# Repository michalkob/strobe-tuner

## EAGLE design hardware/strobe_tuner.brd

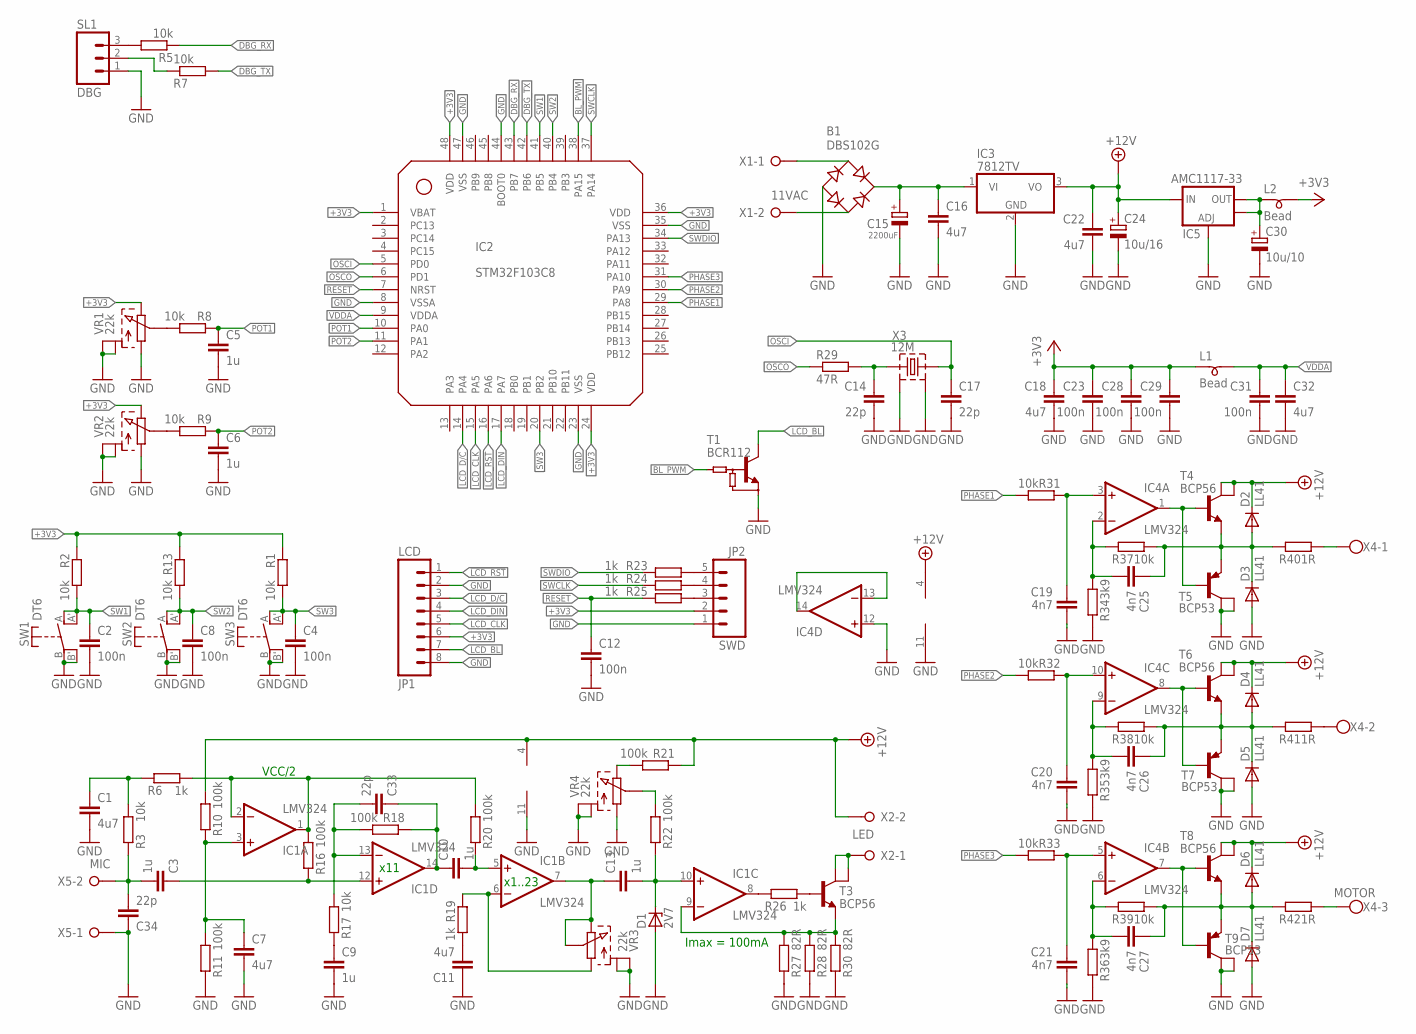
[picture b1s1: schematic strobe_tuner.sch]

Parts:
B1: DBS102G; DBS
C1, C7, C11, C16, C18, C22, C32: 4u7; 1206
C2, C4, C8, C12, C23, C28, C29, C31: 100n; 0805
C3, C5, C6, C9, C10, C13: 1u; 1206
C14, C17, C33, C34: 22p; 0805
C15: 2200uF; E5-13
C19, C20, C21, C25, C26, C27: 4n7; 0805
C24: 10u/16; B/3528-21W
C30: 10u/10; A/3216-18R
D1: 2V7; SOT23
D2, D3, D4, D5, D6, D7: LL41; SOD80C
IC1, IC4: LMV324; SO14
IC2: STM32F103C8; LQFP48
IC3: 7812TV; TO220V
IC5: AMC1117-33; SOT223
JP1: LCD; 1X08
JP2: SWD; 1X05_LOCK_LONGPADS
L1, L2: Bead; 0805
R1, R2, R3, R5, R7, R8, R9, R13, R17, R31, R32, R33, R37, R38, R39: 10k; 0805
R6, R19, R23, R24, R25, R26: 1k; 0805
R10, R11, R16, R18, R20, R21, R22: 100k; 0805
R27, R28, R30: 82R; 0805
R29: 47R; 0805
R34, R35, R36: 3k9; 0805
R40, R41, R42: 1R; 0805
SL1: DBG; 03P
SW1, SW2, SW3: DT6; D6R
T1: BCR112; SOT23
T3, T4, T6, T8: BCP56; SOT223
T5, T7, T9: BCP53; SOT223
VR1, VR2, VR3, VR4: 22k; R122KNP
X1: 11VAC; W237-132
X2: LED; W237-132
X3: 12M; CPFX-104
X4: MOTOR; W237-103
X5: MIC; W237-132

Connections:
!LCD_RST: IC2.16 (PA6), JP1.1
+3V3: C18.1, C23.1, C28.1, C29.1, IC2.1 (VBAT), IC2.24 (VDD), IC2.36 (VDD), IC2.48 (VDD), JP1.6, JP2.2, L1.2 (1), L2.1 (2), R1.1, R2.1, R13.1, VR1.CW (E), VR2.CW (E)
+12V: C22.1, C24.+, D2.C, D4.C, D6.C, IC1.4 (V+), IC3.3 (VO), IC4.4 (V+), IC5.3 (IN), R10.2, R21.1, T4.2 (C), T4.4 (C1), T6.2 (C), T6.4 (C1), T8.2 (C), T8.4 (C1), X2.2
BL_PWM: IC2.38 (PA15), T1.1 (B)
DBG_RX: IC2.43 (PB7), R5.1
DBG_TX: IC2.42 (PB6), R7.2
GND: B1.-, C1.2, C2.2, C4.2, C5.2, C6.2, C7.2, C8.2, C9.2, C11.1, C12.2, C14.2, C15.-, C16.2, C17.2, C18.2, C19.2, C20.2, C21.2, C22.2, C23.2, C24.-, C28.2, C29.2, C30.-, C31.2, C32.2, C34.1, D1.1 (A), D3.A, D5.A, D7.A, IC1.11 (V-), IC2.8 (VSSA), IC2.23 (VSS), IC2.35 (VSS), IC2.44 (BOOT0), IC2.47 (VSS), IC3.2 (GND), IC4.11 (V-), IC4.12 (+IN), IC5.1 (ADJ), JP1.2, JP1.8, JP2.1, R11.1, R27.1, R28.1, R30.1, R34.1, R35.1, R36.1, SL1.1, SW1.B (B1), SW1.B' (B2), SW2.B (B1), SW2.B' (B2), SW3.B (B1), SW3.B' (B2), T1.2 (E), T5.2 (C), T5.4 (C1), T7.2 (C), T7.4 (C1), T9.2 (C), T9.4 (C1), VR1.CCW (A), VR1.P$1 (CASE1), VR1.P$2 (CASE2), VR2.CCW (A), VR2.P$1 (CASE1), VR2.P$2 (CASE2), VR3.P$1 (CASE1), VR3.P$2 (CASE2), VR4.CCW (A), VR4.P$1 (CASE1), VR4.P$2 (CASE2), X3.2 (G1), X3.4 (G2), X5.1
LCD_BL: JP1.7, T1.3 (C)
LCD_CLK: IC2.15 (PA5), JP1.5
LCD_D/C: IC2.14 (PA4), JP1.3
LCD_DIN: IC2.17 (PA7), JP1.4
unnamed: C19.1, IC4.3 (+IN), R31.1
unnamed: C20.1, IC4.10 (+IN), R32.1
unnamed: C21.1, IC4.5 (+IN), R33.1
unnamed: C27.1, D6.A, D7.C, R39.2, R42.1, T8.3 (E), T9.3 (E)
unnamed: C1.1, R3.2, R6.1
unnamed: C7.1, IC1.3 (+IN), R10.1, R11.2
unnamed: C3.2, C34.2, R3.1, X5.2
unnamed: C11.2, R19.2
unnamed: R26.2, T3.1 (B)
unnamed: C9.1, R17.1
unnamed: IC4.1 (OUT), T4.1 (B), T5.1 (B)
unnamed: C25.2, IC4.2 (-IN), R34.2, R37.1
unnamed: C26.1, D4.A, D5.C, R38.2, R41.1, T6.3 (E), T7.3 (E)
unnamed: IC4.8 (OUT), T6.1 (B), T7.1 (B)
unnamed: C26.2, IC4.9 (-IN), R35.2, R38.1
unnamed: C33.2, IC1.13 (-IN), R17.2, R18.2
unnamed: IC4.7 (OUT), T8.1 (B), T9.1 (B)
unnamed: C27.2, IC4.6 (-IN), R36.2, R39.1
unnamed: IC1.9 (-IN), R27.2, R28.2, R30.2, T3.3 (E)
unnamed: T3.2 (C), T3.4 (C1), X2.1
unnamed: IC1.8 (OUT), R26.1
unnamed: R40.2, X4.1
unnamed: R41.2, X4.2
unnamed: R42.2, X4.3
unnamed: IC1.1 (OUT), IC1.2 (-IN), R6.2, R16.2, R20.2
unnamed: C10.1, C33.1, IC1.14 (OUT), R18.1
unnamed: C3.1, IC1.12 (+IN), R16.1
unnamed: C13.2, D1.3 (C), IC1.10 (+IN), R22.1
unnamed: IC1.6 (-IN), R19.1, VR3.CCW (A)
unnamed: C13.1, IC1.7 (OUT), VR3.CW (E), VR3.SLIDER (S)
unnamed: R21.2, VR4.CW (E)
unnamed: R9.2, VR2.SLIDER (S)
unnamed: C10.2, IC1.5 (+IN), R20.1
unnamed: R22.2, VR4.SLIDER (S)
unnamed: R7.1, SL1.2
unnamed: R8.2, VR1.SLIDER (S)
unnamed: JP2.5, R23.1
unnamed: C30.+, IC5.2 (OUT), IC5.4 (OUT), L2.2 (1)
unnamed: C25.1, D2.A, D3.C, R37.2, R40.1, T4.3 (E), T5.3 (E)
unnamed: B1.AC1, X1.1
unnamed: B1.AC2, X1.2
unnamed: IC4.13 (-IN), IC4.14 (OUT)
unnamed: R5.2, SL1.3
unnamed: JP2.4, R24.1
unnamed: JP2.3, R25.1
unnamed: C14.1, R29.2, X3.1
OSCI: C17.1, IC2.5 (PD0), X3.3 (2)
OSCO: IC2.6 (PD1), R29.1
PHASE1: IC2.29 (PA8), R31.2
PHASE2: IC2.30 (PA9), R32.2
PHASE3: IC2.31 (PA10), R33.2
POT1: C5.1, IC2.10 (PA0), R8.1
POT2: C6.1, IC2.11 (PA1), R9.1
RESET: C12.1, IC2.7 (NRST), R25.2
SW1: C2.1, IC2.41 (PB5), R2.2, SW1.A (A1), SW1.A' (A2)
SW2: C8.1, IC2.40 (PB4), R13.2, SW2.A (A1), SW2.A' (A2)
SW3: C4.1, IC2.20 (PB2), R1.2, SW3.A (A1), SW3.A' (A2)
SWCLK: IC2.37 (PA14), R24.2
SWDIO: IC2.34 (PA13), R23.2
VDDA: C31.1, C32.1, IC2.9 (VDDA), L1.1 (2)
VIN: B1.+, C15.+, C16.1, IC3.1 (VI)

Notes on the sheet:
VCC/2
x11
x1..23
Imax = 100mA

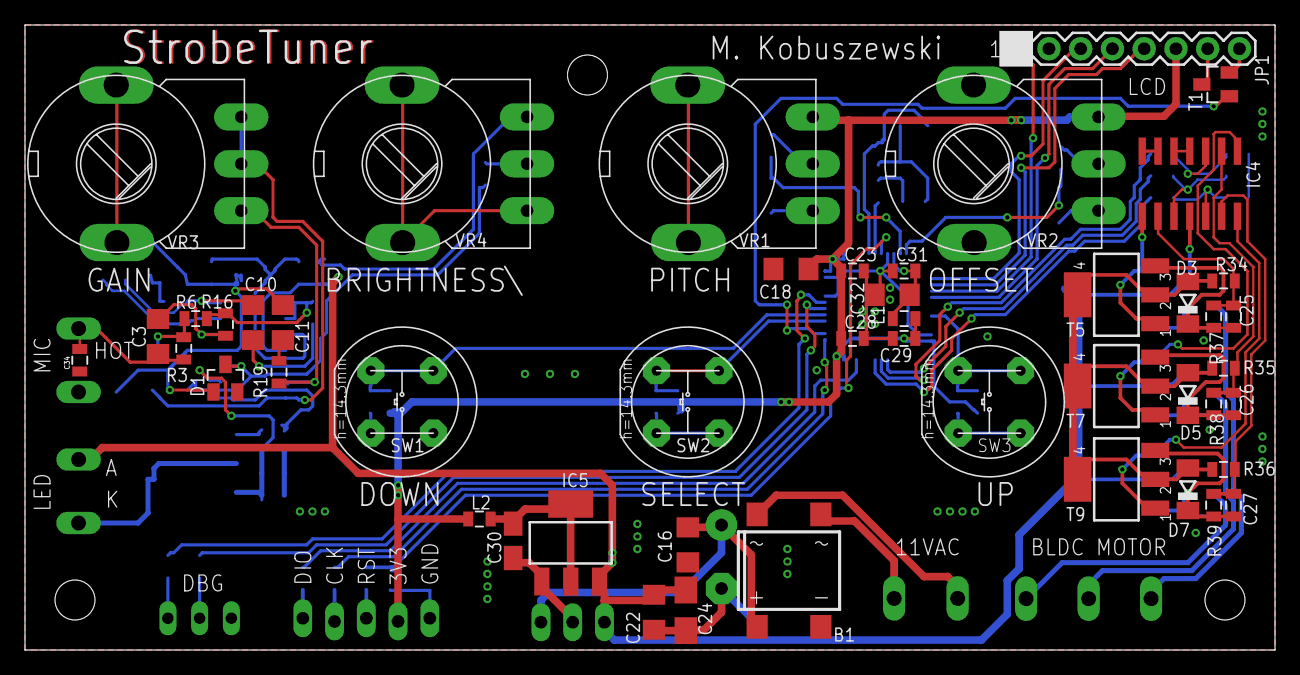
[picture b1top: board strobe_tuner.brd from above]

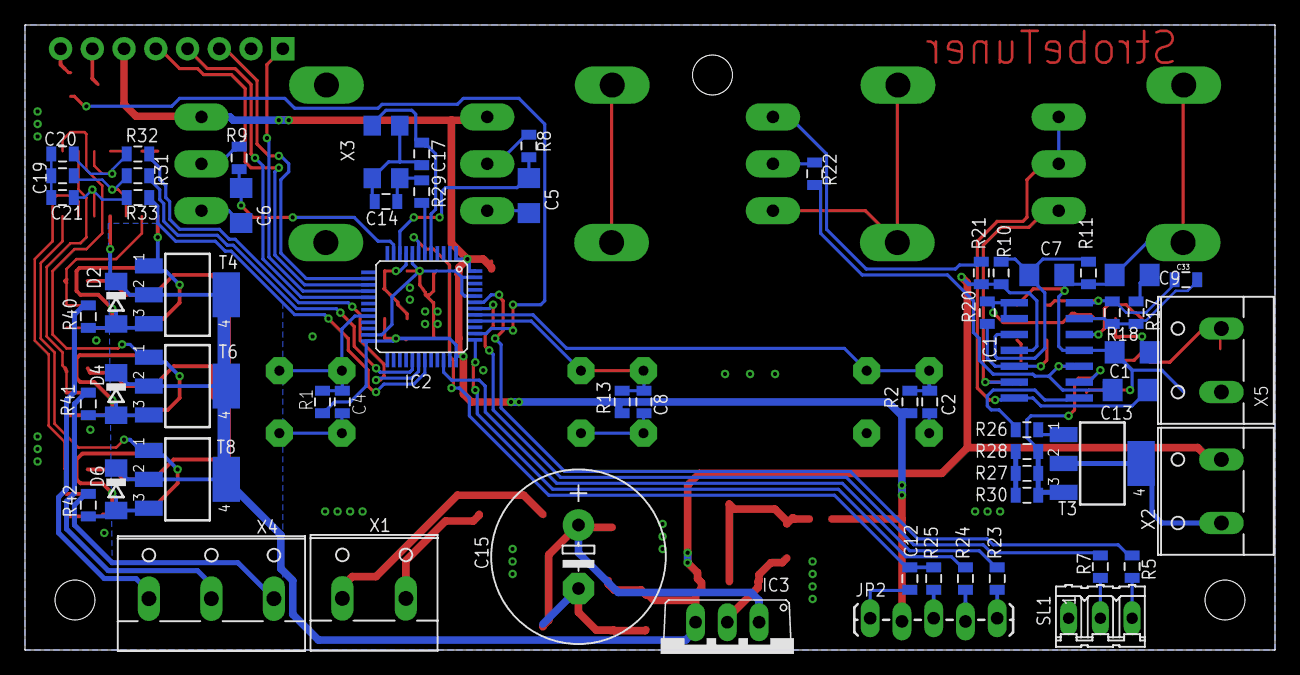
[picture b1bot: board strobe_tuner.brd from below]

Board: 2 copper layers, 100.0 x 50.0 mm, 110 parts (62 on the bottom side), 72 nets.

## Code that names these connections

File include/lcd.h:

//SPI1
// D/C 		PA4
// CLK		PA5
// RST 		PA6
// DIN		PA7
// BL_PWM	PA15 TIM2 CH1

#ifndef LCD_H_
#define LCD_H_

#include "lcd_font.h"

#include "stm32f10x.h"
#include "stm32f10x_spi.h"
#include "system.h"

#define LCD_PIN_RESET       GPIO_Pin_6
#define LCD_PIN_COMMAND     GPIO_Pin_4
#define LCD_PIN_DATA        GPIO_Pin_7
#define LCD_PIN_CLOCK       GPIO_Pin_5
#define	LCD_PIN_BACKLIGHT	GPIO_Pin_15

#define LCD_CMD             0
#define LCD_DATA            1

#define LCD_DISPLAY_BLANK   0x08
#define LCD_DISPLAY_FULL    0x09
#define LCD_DISPLAY_NORMAL  0x0C
#define LCD_DISPLAY_INVERT  0x0D

#define	LCD_BACKLIGHT_STEPS	10
#define	LCD_BACKLIGHT_MUL	200

#define	LCD_CONTRAST_STEPS	10
#define	LCD_CONTRAST_MAX	62
#define	LCD_CONTRAST_MIN	42

#define	LCD_BACKLIGHT_DEF	3
#define	LCD_CONTRAST_DEF	6

typedef struct
{
	uint8_t brightness;
	uint8_t	contrast;
} lcd_settings;

typedef enum
{
	NORMAL,
	INVERTED
} lcd_diplay_mode;

typedef struct
{
	uint8_t frameBuffer[84][6];
	uint8_t x, y;
} lcd_data_struct;

void lcd_init();

void LcdSetBacklight(uint8_t backlight);

void LcdSetContrast(uint8_t contrast);

void LcdApplyCfg();

lcd_settings * lcd_cfg();

void LcdWrite(uint8_t type, uint8_t value);

void LcdRefresh();

void LcdSetXY(uint8_t x, uint8_t y);

void LcdPutSymbol(uint8_t symbol, lcd_diplay_mode mode);

void LcdClearBuf();

void LcdPutInt(uint32_t integer, uint8_t numOfDigits, lcd_diplay_mode mode);

void LcdPutStr(char * string, lcd_diplay_mode mode);

#endif

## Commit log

2016-06-14 :boom::camel: Added .gitattributes & .gitignore files
2016-06-14 Initial commit
    First commit for the repository, contains a tested, working version.
2016-06-14 Moved Eclipse project into /firmware
    Moved Eclipse project into /firmware
2016-06-14 Added hardware files
    Schematic and PCB requires CadSoft EAGLE 7.1
